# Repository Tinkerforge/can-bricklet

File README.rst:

CAN Bricklet
============

This repository contains the firmware source code and the hardware design
files. The documentation generator configs can be found at
https://github.com/Tinkerforge/generators

Repository Content
------------------

software/:
 * examples/: Examples for all supported languages
 * build/: Compiled files
 * src/: Source code of firmware
 * Makefile: Makefile to build project

hardware/:
 * Contains KiCad project files and additionally schematics as PDF

datasheets/:
 * Contains datasheets for sensors and complex ICs that are used

Hardware
--------

The hardware is designed with the open source EDA Suite KiCad
(http://www.kicad.org). Before you are able to open the files,
you have to install the Tinkerforge kicad-libraries
(https://github.com/Tinkerforge/kicad-libraries). You can either clone
them directly in hardware/ or clone them in a separate folder and
symlink them into hardware/
(ln -s kicad_path/kicad-libraries project_path/hardware). After that you
can open the .pro file in hardware/ with KiCad and from there view and
modify the schematics and the PCB layout.

Software
--------

If you want to do your own Brick/Bricklet firmware development we highly
recommend that you use our build environment setup script and read the
tutorial (https://www.tinkerforge.com/en/doc/Tutorials/Tutorial_Build_Environment/Tutorial.html).

To compile the C code we recommend you to install the newest GNU Arm Embedded
Toolchain (https://launchpad.net/gcc-arm-embedded/+download).
You also need to install bricklib (https://github.com/Tinkerforge/bricklib)
and brickletlib (https://github.com/Tinkerforge/brickletlib).

You can either clone it directly in software/src/ or clone it in a
separate folder and symlink it into software/src/
(ln -s bricklib_path/bricklib project_path/software/src/ and
ln -s brickletlib_path/brickletlib project_path/software/src/).
Finally make sure to have CMake installed
(http://www.cmake.org/cmake/resources/software.html).

After that you can build the firmware by invoking make in software/.
The firmware (.bin) can then be found in software/build/ and uploaded
with brickv (click button "Flashing" on start screen).

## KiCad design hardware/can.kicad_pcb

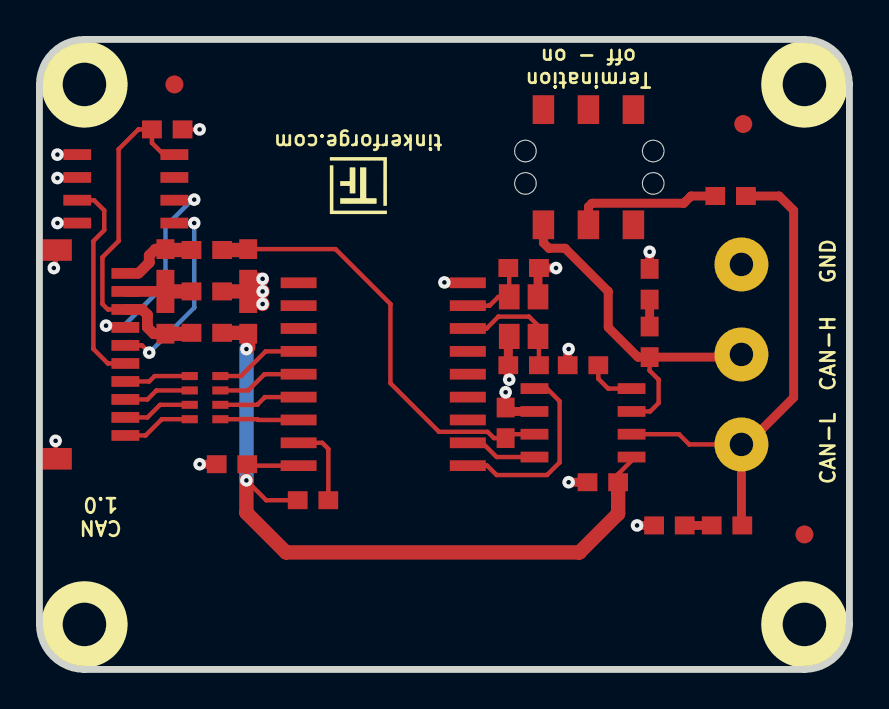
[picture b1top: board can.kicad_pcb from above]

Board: 2 copper layers, 45.0 x 35.0 mm, 37 parts (0 on the bottom side), 28 nets.

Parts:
C1, C2, C3, C4, C5, C7, C9, C10: 100nF; C0603E
C6, C8: DNP; C0603E
C11, C12: 470pF; C0603E
FB1, FB2: FILTER; C0603E
Fiducial_Mark: VAL**; Fiducial_Mark
Fiducial_Mark#2, Fiducial_Mark#3: VAL**; Fiducial_Mark
K1: CONN_3; AKL_5_3
P1: CON-SENSOR
R1: 0; R0603E
R2: 10k; R0603E
R3: 1k; R0603E
R4, R5, R6: 120; R0603E
RP1: 100; 0603X4
SW1: Termination; SLIDE_SWITCH
U1: M24C64; SOIC8
U2: MCP2515; SOIC-18
U3: MCP2562; SOIC8
U4, U5, U6, U7: DRILL; DRILL_NP
VAL: WEEE_7mm
VAL#2: CE_5mm
X1: 16MHz; CRYSTAL_3225

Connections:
3V3: C2.2, C7.1, FB2.1, P1.3, U1.8
+5V: C3.2, C10.1, FB1.2, U3.3
GND: C3.1, C4.1, C5.2, C6.2, C7.2, C8.2, C9.2, C10.2, C11.2, C12.2, K1.1, P1.EP, R1.1, R3.1, U1.1, U1.2, U1.4, U2.9, U3.2, X1.3
unnamed: C1.1, C2.1, P1.2, R1.2
unnamed: C1.2, FB1.1, P1.1
unnamed: C6.1, U2.7, X1.1
unnamed: C8.1, U2.8, X1.2
unnamed: C11.1, R4.1
unnamed: C12.1, R5.1
unnamed: K1.2, R5.2, SW1.1, U3.7
unnamed: K1.3, R4.2, R6.1, U3.6
unnamed: P1.6, U1.3
unnamed: P1.7, RP1.5
unnamed: P1.8, RP1.6
unnamed: P1.9, RP1.7
unnamed: P1.10, RP1.8
unnamed: R2.1, U2.17
unnamed: R3.2, U3.8
unnamed: R6.2, SW1.2
unnamed: RP1.1, U2.16
unnamed: RP1.2, U2.15
unnamed: RP1.3, U2.14
unnamed: RP1.4, U2.13
unnamed: U2.1, U3.1
unnamed: U2.2, U3.4
SCL: P1.4, U1.6
SDA: P1.5, U1.5
VCC: C4.2, C5.1, C9.1, FB2.2, R2.2, U2.18, U3.5

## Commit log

2015-11-10 add readme and License file
2015-11-10 rs232 bricklet data copied, schematic adapted to CAN
2015-11-11 footprints for all symbols added
2015-11-11 fully routed
2015-11-17 fix discription
2016-02-01 add pullup resistor for reset
2016-02-05 Add initial software, not feature-complete yet
2016-02-09 Add wIP marker
2016-02-11 Unify function naming
2016-02-11 Add frame-read callback
2016-02-11 Optimize SPI communication in tick
    To make it fit better into the 200µs timeslice.
2016-02-12 Add get_error_log function
2016-02-12 Fix RXM defines
2016-02-12 Remove unused code
2016-02-12 Fix extended identifier reconstruction
2016-02-12 Ignore data registers for received remote frames
2016-02-12 First read then write to avoid read register overflow in loopback mode
2016-02-12 Avoid false-positive TXB0 header check
    This could happens if the first frame to be written is a standard data
    frame with identifier 0 and no data. In this case the TXB0 header would
    be all zero. In this case the header would not be written und result in
    sending an undefined frame, because the TXB0 registers are undefined
    after a reset.
2016-02-12 Don't write unnecessary data bytes for remote frames
2016-02-15 Fix for loop condition
2016-02-15 Fix value of unused register constant
2016-02-15 Convert all negative write timeout value to -1
2016-02-15 Force extended identifer to be 0 when writing standard frames
    Also don't assume that the frame length is a 4 bit value.
2016-02-15 Reorder BrickContext members to make them fit unpacked
2016-02-15 Cache BC to reduce code size
2016-02-17 Add read filter and timeout handling
2016-02-17 More comments
2016-02-18 Reorder get_error_log parameter
2016-03-04 remove serial connector
2016-03-22 more space between resistors and terminal
2016-03-22 fix can-h/can-l labeling
2016-03-22 adapt filter values
2016-06-17 add schematic
2016-06-28 Fix typos
2016-06-28 Removed unused code
2016-06-28 Add examples
2016-06-29 Add datasheets
2016-06-29 Add CE logo errata
2016-06-29 perl: Add missing my qualifier
2016-07-01 Make the change UID comment more explicit
2016-07-13 Add changelog date and commit after the fact
2016-07-14 Remove WIP marker
2017-04-13 csharp: Adapt example
2017-04-20 shell: Adapt example
2017-06-02 octave: Use javaObject instead of deprecated java_new
2017-08-01 Add 3d information (final)
2017-08-01 Add 3d model (*.step & *.FCStd)
2017-11-30 Update examples from generator
2017-12-07 mathematica: Also generate .nb files
2018-02-19 javascript: Close div tag correctly
2018-02-20 Cleanup KiCad libraries config
    Ensure LibDir=kicad-libraries and LibName1=tinkerforge.
    Remove special library.
2018-05-24 perl: Use strict in examples
2018-05-29 mathematica: Use proper namespace
2018-06-05 examples: Avoid temporary variables if possible
2018-06-05 Fix typos in examples
2018-07-11 Add Makefile with docker support
2018-07-11 Update directory structure and build instructions
2018-07-11 Remove obsolete generate_makefile scripts
2018-11-06 Add rust examples
2018-11-07 rust: Accept host names for ip connection, fix naming inconsistencies
2018-11-07 rust: Rename callback receivers.
2018-12-14 Add go examples.
2018-12-18 go: Change import path.
2018-12-18 go: Change import path again.
2018-12-20 rust: Reformat examples.
2019-01-24 mqtt: Add examples.
2019-01-24 mqtt: Remove executable bit in example permissions.
2019-01-24 go: Minor example fixes.
2019-08-22 c: Adapt to bindings changes
2020-01-14 examples: Use python3 input by default.
2020-02-28 Add frame readable callback.
2020-02-28 Change frame readable ccf to new style.
2020-02-28 Increase firmware version.
2020-02-28 Append to changelog.
2020-02-28 Add commit ref to changelog.
2020-03-17 Whitespace
2020-03-17 rust: Update to new skeleton
2020-03-17 examples: Add constant translation for frame type
2020-03-18 delphi: Adapt naming override
2020-03-18 Fix typo
2020-04-03 Add openHAB examples.
2021-10-25 Update KiCad link
    https://www.kicad.org/blog/2021/10/Avoid-links-to-former-kicad-domain/
2022-07-06 Add license files.

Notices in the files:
hardware/can.kicad_pcb:
Licensed under CERN OHL v.1.1
Copyright (©) 2015, B.Nordmeyer
Copyright Tinkerforge GmbH 2016.
This documentation describes Open Hardware and is licensed under the
CERN OHL v. 1.1.
